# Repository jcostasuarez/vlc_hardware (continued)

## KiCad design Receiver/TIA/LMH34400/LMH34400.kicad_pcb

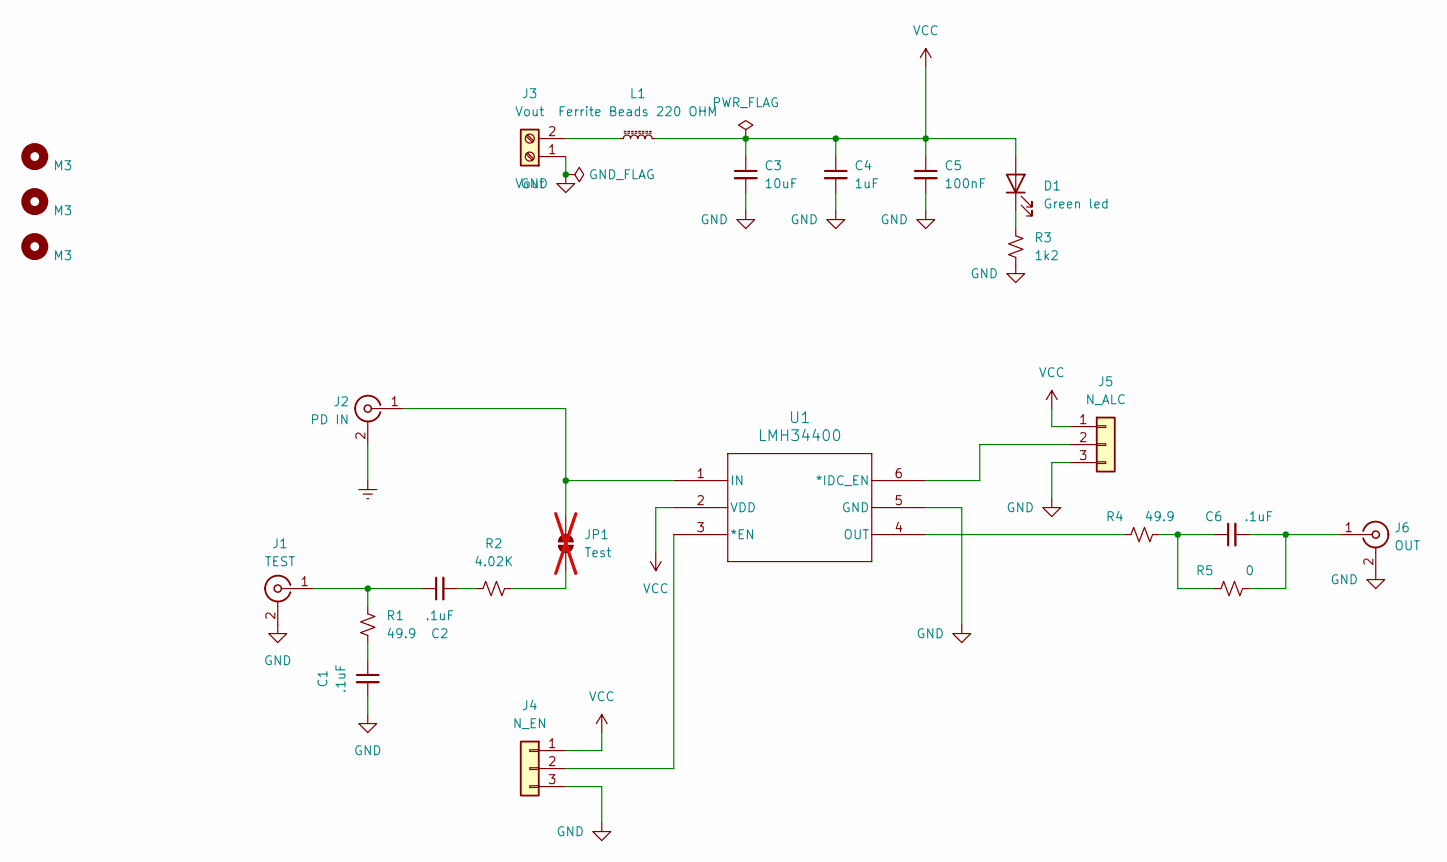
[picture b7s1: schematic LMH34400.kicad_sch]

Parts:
C1, C2, C6: .1uF; C_0402_1005Metric_Pad0.74x0.62mm_HandSolder; Manufacturer Part Number 530L104KT16; Mouser Part Number 581-530L104KT16
C3: 10uF; C_0603_1608Metric_Pad1.08x0.95mm_HandSolder; Manufacturer Part Number GRM188Z71A106MA73D; Mouser Part Number 81-GRM188Z71A106MA3D
C4: 1uF; C_0603_1608Metric_Pad1.08x0.95mm_HandSolder; Manufacturer Part Number CL10B105KP8NNNC; Mouser Part Number 187-CL10B105KP8NNNC
C5: 100nF; C_0603_1608Metric_Pad1.08x0.95mm_HandSolder; Manufacturer Part Number CL10B104KO8NFNC; Mouser Part Number 187-CL10B104KO8NFNC
D1: Green led; LED_0603_1608Metric; Manufacturer Part Number 150060VS75000; Mouser Part Number 710-150060VS75000
H1, H2, H3: M3; MountingHole_3.2mm_M3_DIN965
J1: TEST; SMA_Samtec_SMA-J-P-X-ST-EM1_EdgeMount
J2: PD IN; SMA_Samtec_SMA-J-P-X-ST-EM1_EdgeMount
J3: Vout; TerminalBlock_Phoenix_MKDS-1,5-2_1x02_P5.00mm_Horizontal
J4: N_EN; PinHeader_1x03_P2.54mm_Vertical
J5: N_ALC; PinHeader_1x03_P2.54mm_Vertical
J6: OUT; SMA_Samtec_SMA-J-P-X-ST-EM1_EdgeMount
JP1: Test; R_0603_1608Metric_Pad0.98x0.95mm_HandSolder; Manufacturer Part Number MCT0603MZ0000ZP500; Mouser Part Number 594-MCT0603MZ0000ZP5; not fitted
L1: Ferrite Beads 220 OHM; L_0603_1608Metric_Pad1.05x0.95mm_HandSolder; Manufacturer Part Number BLM18KG221SN1D; Mouser Part Number 81-BLM18KG221SN1D
R1, R4: 49.9; R_0603_1608Metric_Pad0.98x0.95mm_HandSolder; Manufacturer Part Number MCT06030C4999FP500; Mouser Part Number 594-MCT06030C4999FP5
R2: 4.02K; R_0603_1608Metric_Pad0.98x0.95mm_HandSolder; Manufacturer Part Number MCT06030C4021FP500; Mouser Part Number 594-MCT06030C4021FP5
R3: 1k2; R_0603_1608Metric_Pad0.98x0.95mm_HandSolder; Manufacturer Part Number CRCW06031K20FKEA; Mouser Part Number 71-CRCW0603-1.2K-E3
R5: 0; R_0603_1608Metric_Pad0.98x0.95mm_HandSolder; Manufacturer Part Number MCT0603MZ0000ZP500; Mouser Part Number 594-MCT0603MZ0000ZP5
U1: LMH34400; SOT5X3-6_DRL_TEX; Manufacturer Part Number LMH34400IDRLR; Mouser Part Number 595-LMH34400IDRLR

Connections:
GND: C1.2, C3.2, C4.2, C5.2, J1.2 (Ext), J2.2 (Ext), J3.1, J4.3, J5.3, J6.2 (Ext), R3.2, U1.5 (GND)
unnamed: C1.1, R1.2
unnamed: C2.2, R2.1
unnamed: C6.1, R4.2, R5.1
unnamed: D1.1 (K), R3.1
unnamed: C2.1, J1.1 (In), R1.1
unnamed: J2.1 (In), JP1.2 (B), U1.1 (IN)
unnamed: J3.2, L1.1
unnamed: J4.2, U1.3 (*EN)
unnamed: J5.2, U1.6 (*IDC_EN)
unnamed: C6.2, J6.1 (In), R5.2
unnamed: JP1.1 (A), R2.2
unnamed: R4.1, U1.4 (OUT)
VCC: C3.1, C4.1, C5.1, D1.2 (A), J4.1, J5.1, L1.2, U1.2 (VDD)

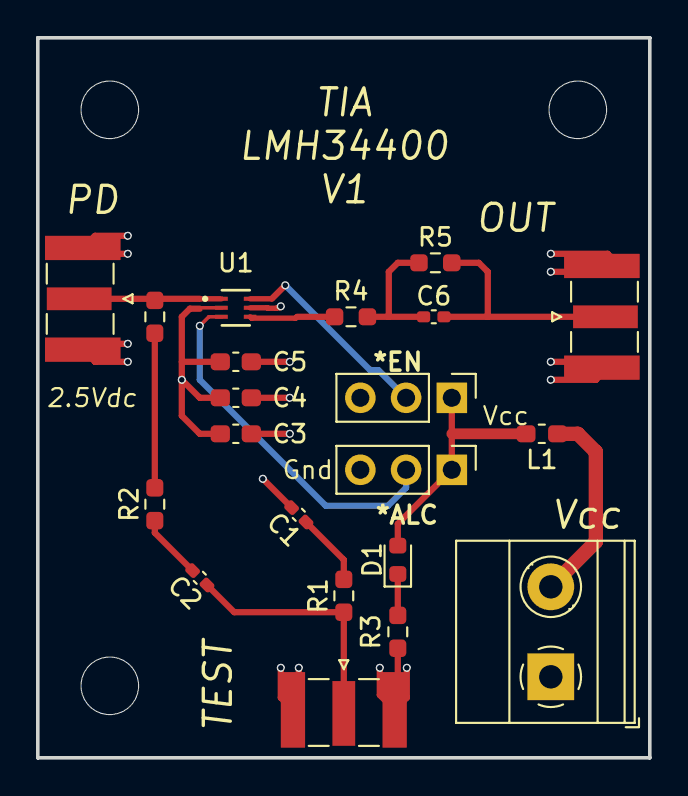
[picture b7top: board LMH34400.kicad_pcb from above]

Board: 4 copper layers, 34.0 x 40.0 mm, 24 parts (0 on the bottom side), 14 nets.

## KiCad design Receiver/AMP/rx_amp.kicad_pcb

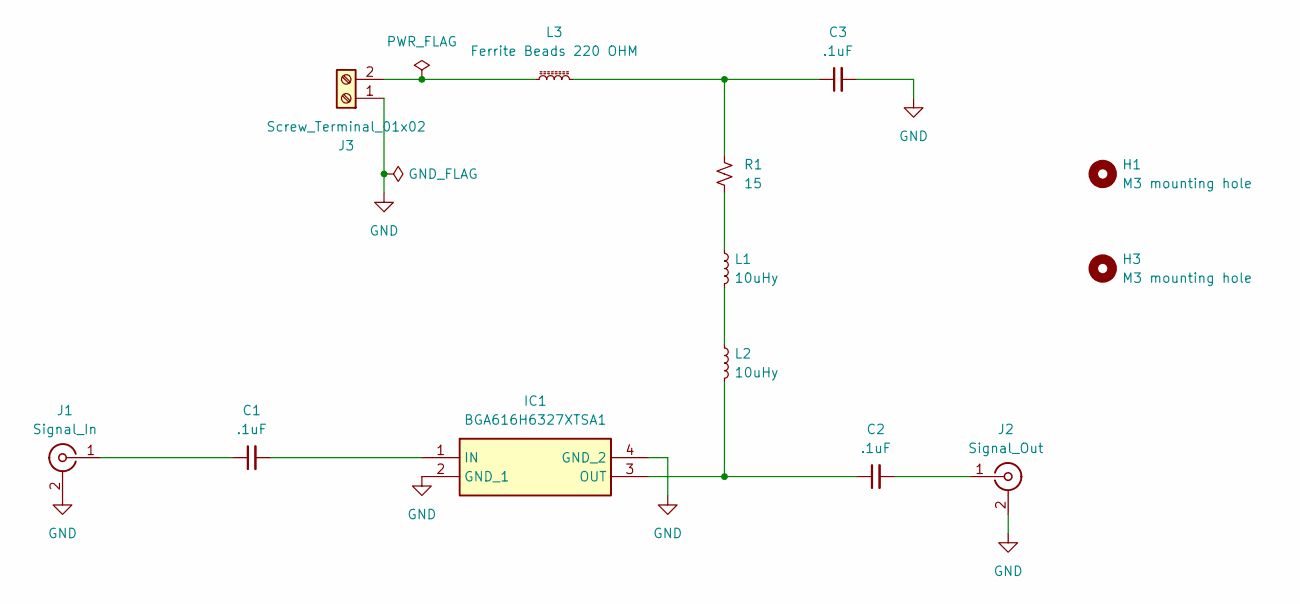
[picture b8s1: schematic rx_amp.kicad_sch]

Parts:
C1, C2, C3: .1uF; C_0402_1005Metric_Pad0.74x0.62mm_HandSolder; Mouser Part Number 581-530L104KT16
H1, H3: M3 mounting hole; MountingHole_3.2mm_M3_DIN965
IC1: BGA616H6327XTSA1; Mouser Part Number 726-BGA616H6327XTSA1
J1: Signal_In; SMA_Samtec_SMA-J-P-X-ST-EM1_EdgeMount
J2: Signal_Out; SMA_Samtec_SMA-J-P-X-ST-EM1_EdgeMount
J3: Screw_Terminal_01x02; TerminalBlock_RND_205-00001_1x02_P5.00mm_Horizontal
L1, L2: 10uHy; L_0603_1608Metric_Pad1.05x0.95mm_HandSolder; Mouser Part Number 81-LQM18DZ100M70L
L3: Ferrite Beads 220 OHM; L_0603_1608Metric_Pad1.05x0.95mm_HandSolder; Mouser Part Number 81-BLM18KG221SN1D
R1: 15; L_0603_1608Metric_Pad1.05x0.95mm_HandSolder; Mouser Part Number 710-560112116150

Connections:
GND: C3.2, IC1.2 (GND_1), IC1.4 (GND_2), J1.2 (Ext), J2.2 (Ext), J3.1
unnamed: C3.1, L3.2, R1.1
unnamed: C1.2, IC1.1 (IN)
unnamed: C2.1, IC1.3 (OUT), L2.2
unnamed: C1.1, J1.1 (In)
unnamed: C2.2, J2.1 (In)
unnamed: J3.2, L3.1
unnamed: L1.1, R1.2
unnamed: L1.2, L2.1

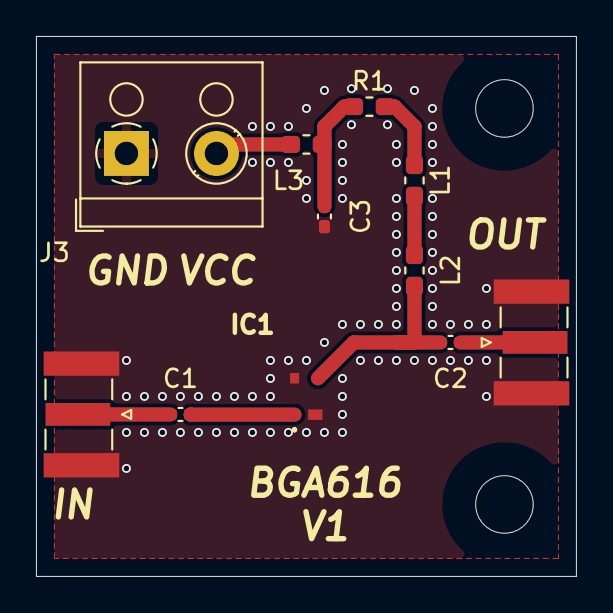
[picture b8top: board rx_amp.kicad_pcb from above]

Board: 2 copper layers, 30.0 x 30.0 mm, 13 parts (0 on the bottom side), 9 nets.

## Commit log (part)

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2025-03-18 Final plots for tesis
